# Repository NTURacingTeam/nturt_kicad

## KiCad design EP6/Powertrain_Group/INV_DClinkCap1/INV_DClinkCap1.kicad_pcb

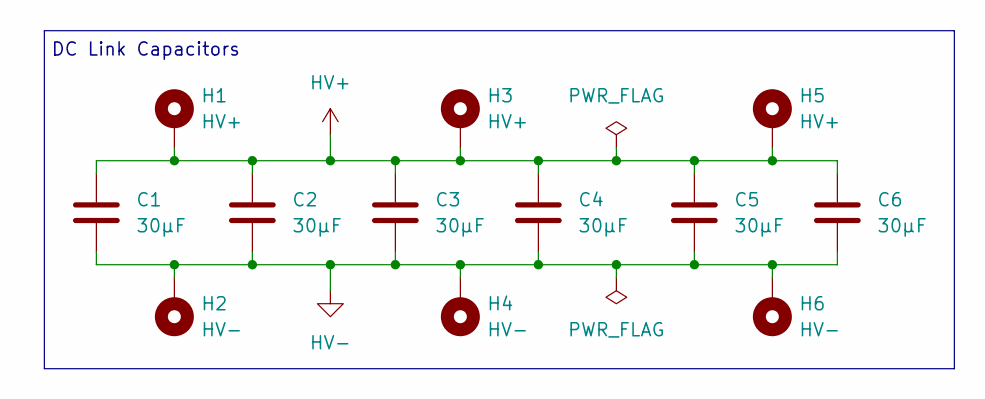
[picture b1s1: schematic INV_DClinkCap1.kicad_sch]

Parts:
C1, C2, C3, C4, C5, C6: 30µF; C4AQJBW5300M3JJ
H1, H3, H5: HV+; MountingHole_5.5mm_Pad_Via_15mm_square
H2, H4, H6: HV-; MountingHole_5.5mm_Pad_Via_15mm_square

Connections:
HV+: C1.1, C2.1, C3.1, C4.1, C5.1, C6.1, H1.1, H3.1, H5.1
HV-: C1.2, C2.2, C3.2, C4.2, C5.2, C6.2, H2.1, H4.1, H6.1

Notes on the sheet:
DC Link Capacitors

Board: 4 copper layers, 12 parts (3 on the bottom side), 2 nets, no tracks yet.

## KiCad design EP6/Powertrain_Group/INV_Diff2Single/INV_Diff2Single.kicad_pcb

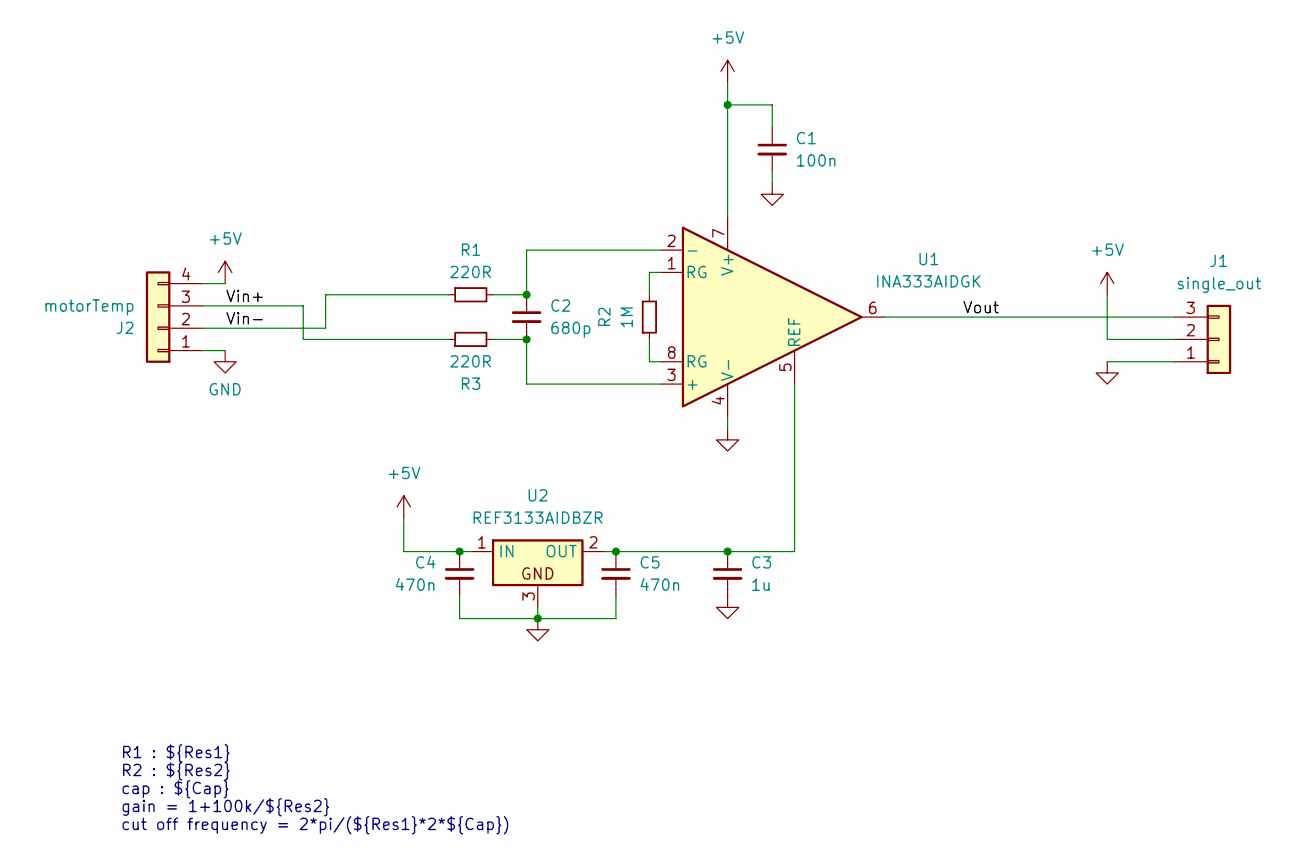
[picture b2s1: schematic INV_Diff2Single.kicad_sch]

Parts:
C1: 100n; C_0402_1005Metric
C2: 680p; C_0402_1005Metric
C3: 1u; C_0402_1005Metric
C4, C5: 470n; C_0603_1608Metric
J1: single_out; PinHeader_1x03_P2.00mm_Horizontal
J2: motorTemp; PinHeader_1x04_P2.54mm_Horizontal
R1, R3: 220R; R_0402_1005Metric
R2: 1M; R_0402_1005Metric
U1: INA333AIDGK; MSOP-8_3x3mm_P0.65mm
U2: REF3133AIDBZR; SOT-23

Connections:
+5V: C1.1, C4.1, J1.2, J2.4, U1.7 (V+), U2.1 (IN)
/Vin+: J2.3, R3.1
/Vin-: J2.2, R1.1
/Vout: J1.3, U1.6
GND: C1.2, C3.2, C4.2, C5.2, J1.1, J2.1, U1.4 (V-), U2.3
unnamed: R2.1, U1.8 (RG)
unnamed: R2.2, U1.1 (RG)
unnamed: C2.2, R3.2, U1.3 (+)
unnamed: C2.1, R1.2, U1.2 (-)
unnamed: C3.1, C5.1, U1.5 (REF), U2.2 (OUT)

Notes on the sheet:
R1 : ${Res1} R2 : ${Res2} cap : ${Cap} gain = 1+100k/${Res2} cut off frequency = 2*pi/(${Res1}*2*${Cap})

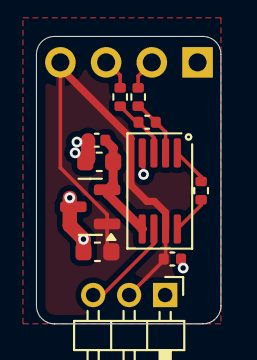
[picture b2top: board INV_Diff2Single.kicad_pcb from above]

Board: 2 copper layers, 10.2 x 16.0 mm, 12 parts (1 on the bottom side), 10 nets.

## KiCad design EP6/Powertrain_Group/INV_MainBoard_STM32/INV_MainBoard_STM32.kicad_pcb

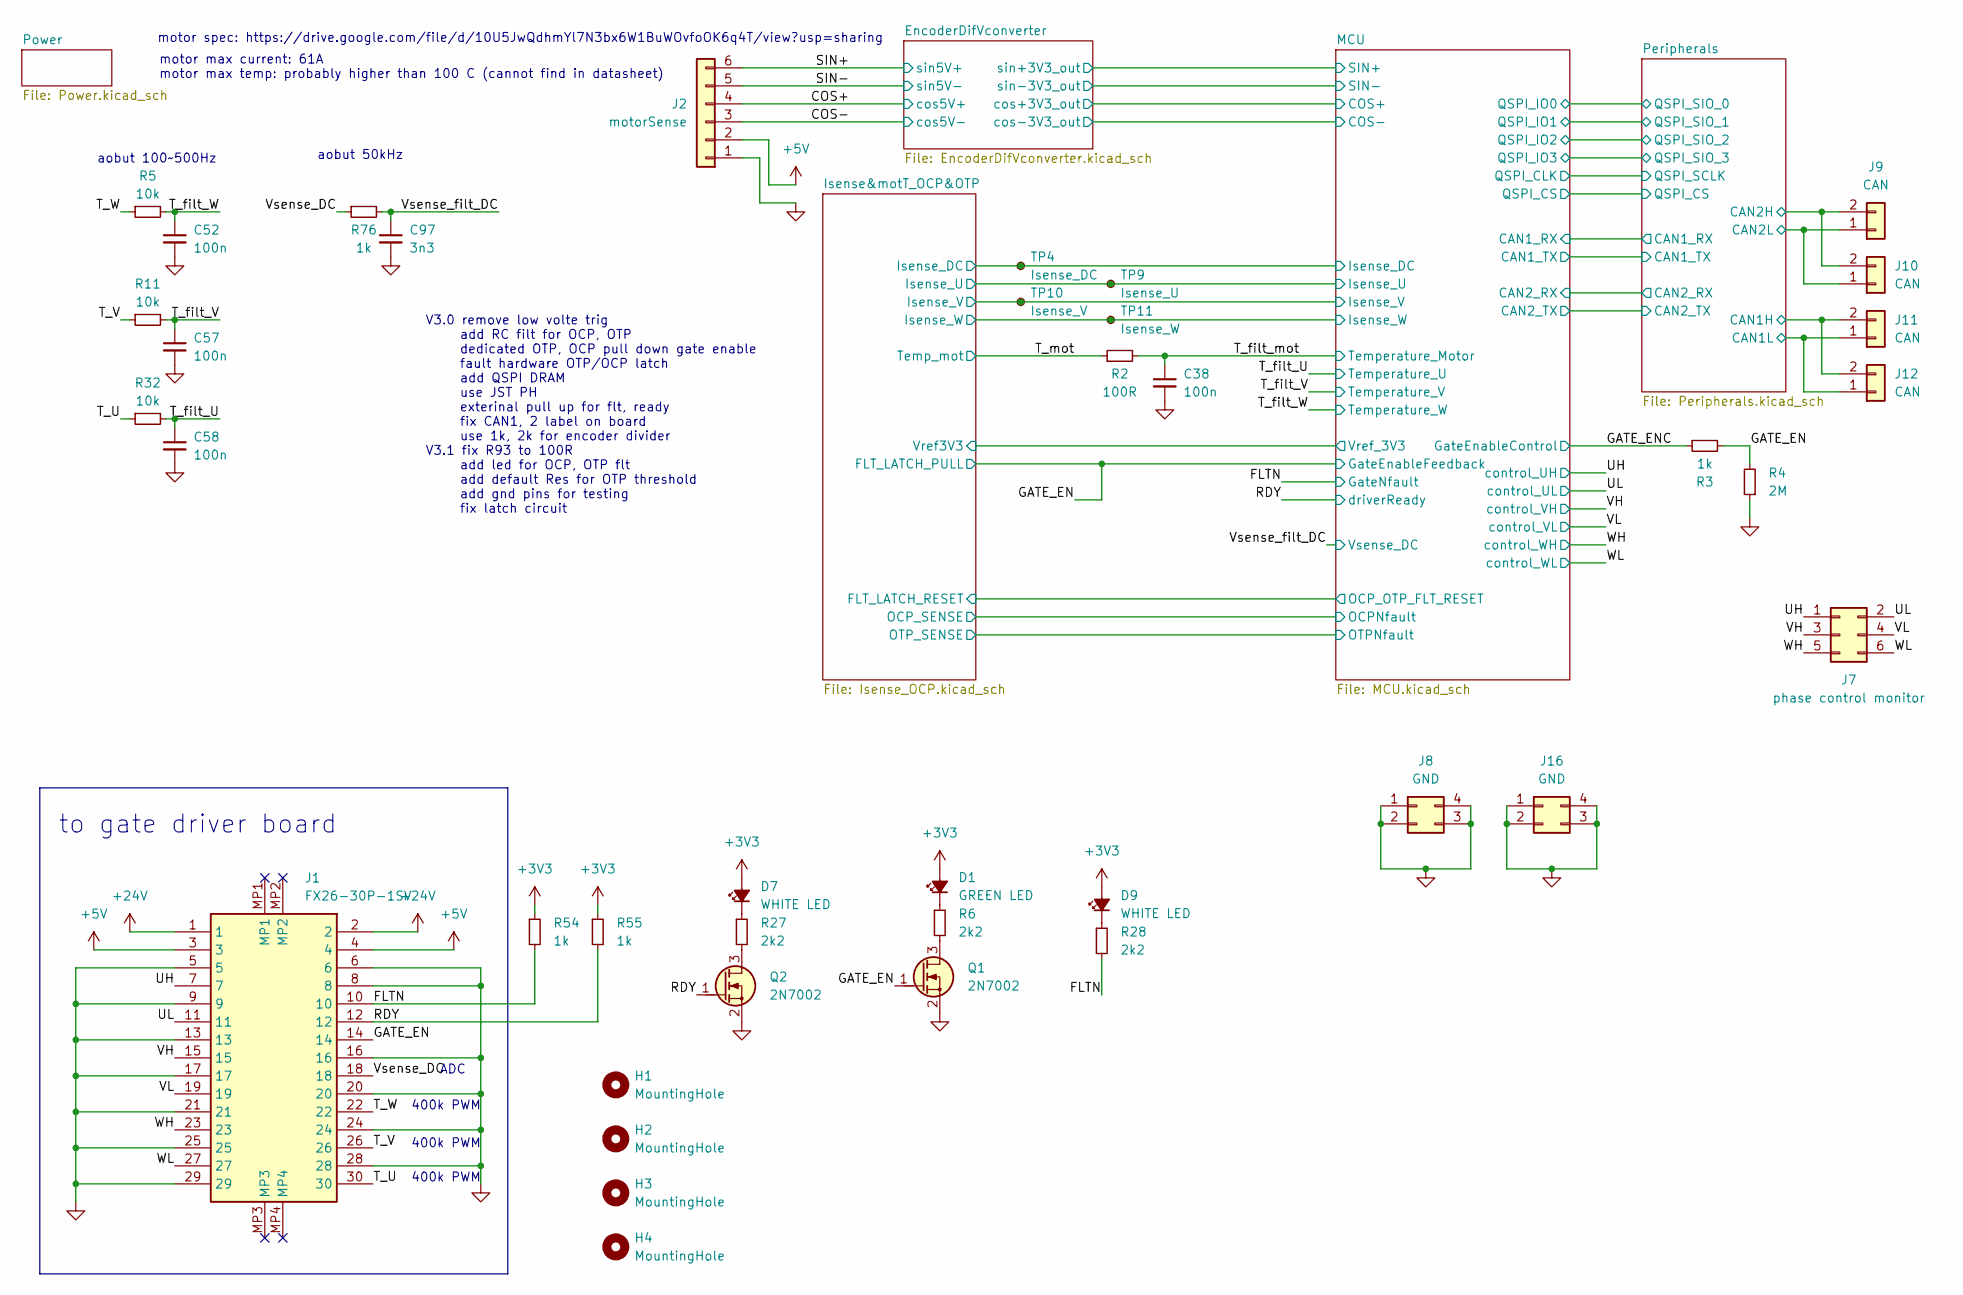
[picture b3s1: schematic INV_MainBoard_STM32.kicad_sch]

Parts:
C38, C52, C57, C58: 100n; C_0402_1005Metric
C97: 3n3; C_0402_1005Metric
D1: GREEN LED; LED_0805_2012Metric
D7, D9: WHITE LED; LED_0805_2012Metric
H1, H2, H3, H4: MountingHole; MountingHole_3.2mm_M3
J1: FX26-30P-1SV; FX2630P1SV; Mouser Part Number 798-FX2630P1SV
J2: motorSense; JST_PH_B6B-PH-K_1x06_P2.00mm_Vertical
J7: phase control monitor; PinHeader_2x03_P2.54mm_Vertical
J8, J16: GND; PinHeader_2x02_P2.54mm_Vertical
J9, J10, J11, J12: CAN; JST_XH_B2B-XH-A_1x02_P2.50mm_Vertical
Q1, Q2: 2N7002; SOT-23
R2: 100R; R_0402_1005Metric
R3, R54, R55, R76: 1k; R_0402_1005Metric
R4: 2M; R_0603_1608Metric
R5, R11, R32: 10k; R_0402_1005Metric
R6, R27, R28: 2k2; R_0402_1005Metric
TP4: Isense_DC; TestPoint_Pad_D1.0mm
TP9: Isense_U; TestPoint_Pad_D1.0mm
TP10: Isense_V; TestPoint_Pad_D1.0mm
TP11: Isense_W; TestPoint_Pad_D1.0mm

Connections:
+3V3: D1.2 (A), D7.2 (A), D9.2 (A), R54.1, R55.1; also elsewhere on the board
+5V: J1.3, J1.4, J2.2; also elsewhere on the board
+24V: J1.1, J1.2; also elsewhere on the board
/COS+: J2.4; also elsewhere on the board
/COS-: J2.3; also elsewhere on the board
/FLTN: J1.10, R28.2, R54.2; also elsewhere on the board
/GATE_EN: J1.14, Q1.1 (G), R3.2, R4.2; also elsewhere on the board
/GATE_ENC: R3.1; also elsewhere on the board
/Isense&motT_OCP&OTP/Isense_DC: TP4.1; also elsewhere on the board
/Isense&motT_OCP&OTP/Isense_U: TP9.1; also elsewhere on the board
/Isense&motT_OCP&OTP/Isense_V: TP10.1; also elsewhere on the board
/Isense&motT_OCP&OTP/Isense_W: TP11.1; also elsewhere on the board
/Peripherals/CAN1H: J11.2, J12.2; also elsewhere on the board
/Peripherals/CAN1L: J11.1, J12.1; also elsewhere on the board
/Peripherals/CAN2H: J9.2, J10.2; also elsewhere on the board
/Peripherals/CAN2L: J9.1, J10.1; also elsewhere on the board
/RDY: J1.12, Q2.1 (G), R55.2; also elsewhere on the board
/SIN+: J2.6; also elsewhere on the board
/SIN-: J2.5; also elsewhere on the board
/T_U: J1.30, R32.1
/T_V: J1.26, R11.1
/T_W: J1.22, R5.1
/T_filt_U: C58.1, R32.2; also elsewhere on the board
/T_filt_V: C57.1, R11.2; also elsewhere on the board
/T_filt_W: C52.1, R5.2; also elsewhere on the board
/T_filt_mot: C38.1, R2.2; also elsewhere on the board
/T_mot: R2.1; also elsewhere on the board
/UH: J1.7, J7.1; also elsewhere on the board
/UL: J1.11, J7.2; also elsewhere on the board
/VH: J1.15, J7.3; also elsewhere on the board
/VL: J1.19, J7.4; also elsewhere on the board
/Vsense_DC: J1.18, R76.1
/Vsense_filt_DC: C97.1, R76.2; also elsewhere on the board
/WH: J1.23, J7.5; also elsewhere on the board
/WL: J1.27, J7.6; also elsewhere on the board
GND: C38.2, C52.2, C57.2, C58.2, C97.2, J1.5, J1.6, J1.8, J1.9, J1.13, J1.16, J1.17, J1.20, J1.21, J1.24, J1.25, J1.28, J1.29, J2.1, J8.1, J8.2, J8.3, J8.4, J16.1, J16.2, J16.3, J16.4, Q1.2 (S), Q2.2 (S), R4.1; also elsewhere on the board
unnamed: D1.1 (K), R6.1
unnamed: D7.1 (K), R27.1
unnamed: D9.1 (K), R28.1
unnamed: Q1.3 (D), R6.2
unnamed: Q2.3 (D), R27.2

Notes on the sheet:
motor spec: https://drive.google.com/file/d/10U5JwQdhmYl7N3bx6W1BuWOvfoOK6q4T/view?usp=sharing
400k PWM
to gate driver board
motor max current: 61A motor max temp: probably higher than 100 C (cannot find in datasheet)
V3.0 remove low volte trig add RC filt for OCP, OTP dedicated OTP, OCP pull down gate enable fault hardware OTP/OCP latch add QSPI DRAM use JST PH exterinal pull up for flt, ready fix CAN1, 2 label on board use 1k, 2k for encoder divider V3.1 fix R93 to 100R add led for OCP, OTP flt add default Res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
aobut 50kHz
aobut 100~500Hz
ADC

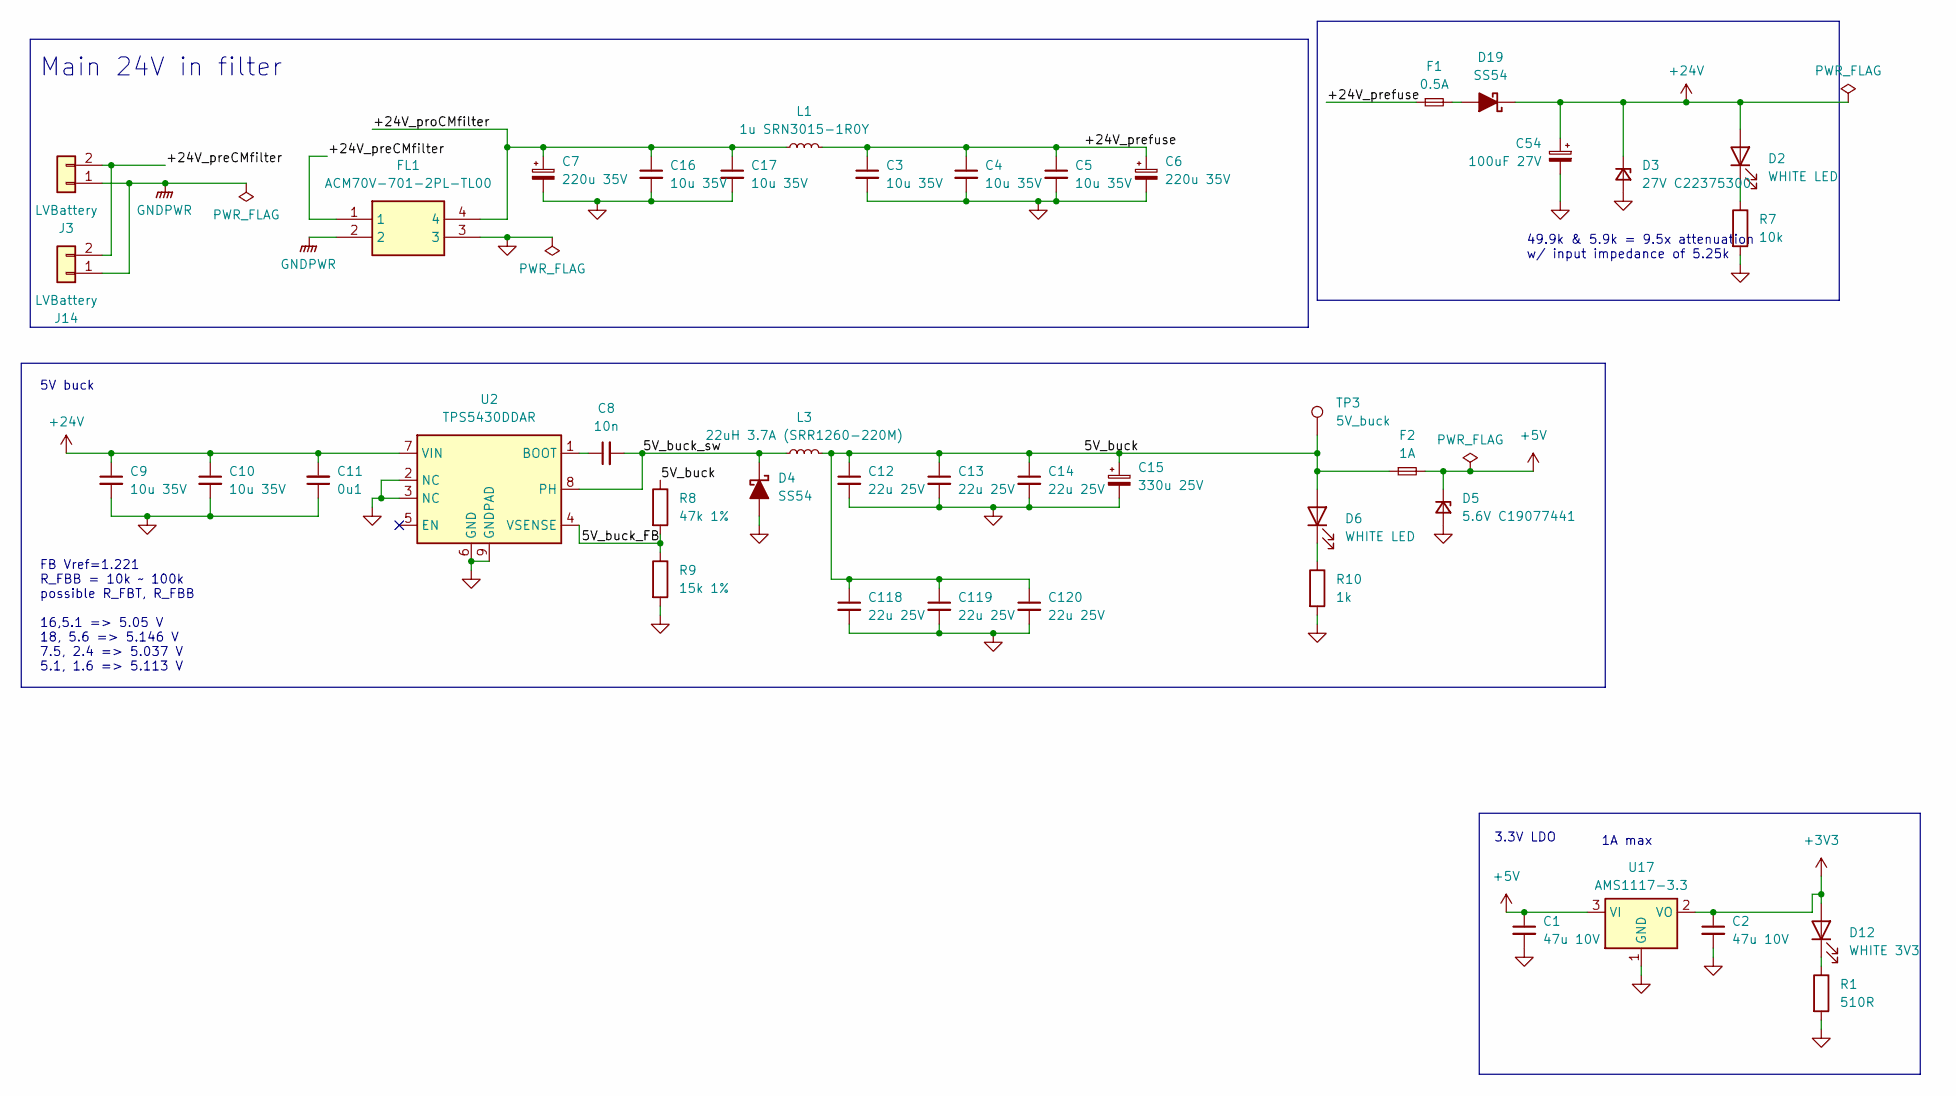
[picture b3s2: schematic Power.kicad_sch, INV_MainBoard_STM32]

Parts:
C1, C2: 47u 10V; C_1206_3216Metric
C3, C4, C5, C9, C10, C16, C17: 10u 35V; C_1206_3216Metric
C6, C7: 220u 35V; CP_Radial_D8.0mm_P3.80mm
C8: 10n; C_0603_1608Metric
C11: 0u1; C_0603_1608Metric
C12, C13, C14, C118, C119, C120: 22u 25V; C_1206_3216Metric
C15: 330u 25V; CP_Radial_D8.0mm_P3.80mm
C54: 100uF 27V; CP_Radial_D10.0mm_P5.00mm
D2, D6: WHITE LED; LED_0603_1608Metric
D3: 27V C22375300; D_SOD-323
D4, D19: SS54; D_SMA
D5: 5.6V C19077441; D_SOD-323
D12: WHITE 3V3; LED_0603_1608Metric
F1: 0.5A; Fuse_1206_3216Metric
F2: 1A; Fuse_1206_3216Metric
FL1: ACM70V-701-2PL-TL00; ACM70V7012PLTL00; Mouser Part Number 810-ACM70V7012PLTL00
J3, J14: LVBattery; JST_VH_B2P-VH_1x02_P3.96mm_Vertical
L1: 1u SRN3015-1R0Y; L_Wuerth_MAPI-3015
L3: 22uH 3.7A (SRR1260-220M); SRR1260A220M
R1: 510R; R_0402_1005Metric
R7: 10k; R_0402_1005Metric
R8: 47k 1%; R_0603_1608Metric
R9: 15k 1%; R_0603_1608Metric
R10: 1k; R_0402_1005Metric
TP3: 5V_buck; TestPoint_Pad_D1.0mm
U2: TPS5430DDAR; TI_SO-PowerPAD-8_ThermalVias
U17: AMS1117-3.3; SOT-223-3_TabPin2

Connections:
+3V3: C2.1, D12.2 (A), U17.2 (VO); also elsewhere on the board
+5V: C1.1, D5.1 (K), F2.2, U17.3 (VI); also elsewhere on the board
+24V: C9.1, C10.1, C11.2, C54.1, D2.2 (A), D3.1 (K), D19.1 (K), U2.7 (VIN); also elsewhere on the board
/Power/5V_buck: C12.1, C13.1, C14.1, C15.1, C118.1, C119.1, C120.1, D6.2 (A), F2.1, L3.2, R8.1, TP3.1
/Power/5V_buck_FB: R8.2, R9.1, U2.4 (VSENSE)
/Power/5V_buck_sw: C8.2, D4.1 (K), L3.1, U2.8 (PH)
/Power/+24V_preCMfilter: FL1.1, J3.2, J14.2
/Power/+24V_prefuse: C3.1, C4.1, C5.1, C6.1, F1.1, L1.2
/Power/+24V_proCMfilter: C7.1, C16.1, C17.1, FL1.4, L1.1
GND: C1.2, C2.2, C3.2, C4.2, C5.2, C6.2, C7.2, C9.2, C10.2, C11.1, C12.2, C13.2, C14.2, C15.2, C16.2, C17.2, C54.2, C118.2, C119.2, C120.2, D3.2 (A), D4.2 (A), D5.2 (A), FL1.3, R1.2, R7.2, R9.2, R10.2, U2.2 (NC), U2.3 (NC), U2.6 (GND), U2.9 (GNDPAD), U17.1 (GND); also elsewhere on the board
GNDPWR: FL1.2, J3.1, J14.1
unnamed: D2.1 (K), R7.1
unnamed: D6.1 (K), R10.1
unnamed: D12.1 (K), R1.1
unnamed: D19.2 (A), F1.2
unnamed: C8.1, U2.1 (BOOT)

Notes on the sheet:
5V buck
49.9k & 5.9k = 9.5x attenuation w/ input impedance of 5.25k
1A max
FB Vref=1.221 R_FBB = 10k ~ 100k possible R_FBT, R_FBB 16,5.1 => 5.05 V 18, 5.6 => 5.146 V 7.5, 2.4 => 5.037 V 5.1, 1.6 => 5.113 V
Main 24V in filter
3.3V LDO

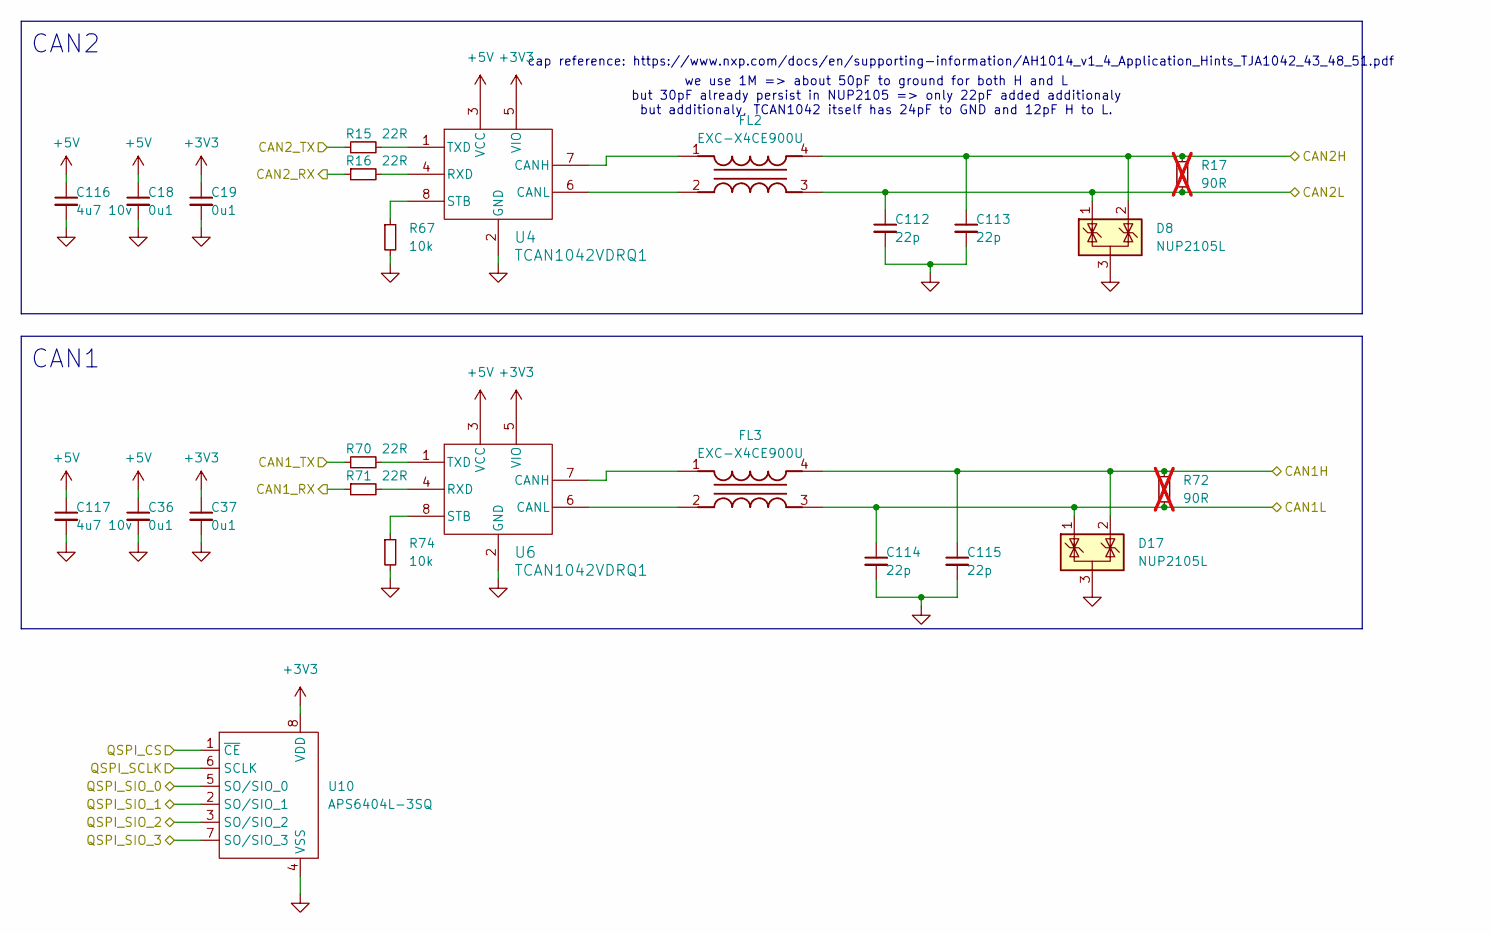
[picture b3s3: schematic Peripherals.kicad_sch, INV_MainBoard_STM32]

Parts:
C18, C19, C36, C37: 0u1; C_0402_1005Metric
C112, C113, C114, C115: 22p; C_0402_1005Metric
C116, C117: 4u7 10v; C_0402_1005Metric
D8, D17: NUP2105L; SOT-23
FL2, FL3: EXC-X4CE900U; EXCX4CE900U; Mouser Part Number 667-EXC-X4CE900U
R15, R16, R70, R71: 22R; R_0402_1005Metric
R17, R72: 90R; R_0402_1005Metric; not fitted
R67, R74: 10k; R_0402_1005Metric
U4, U6: TCAN1042VDRQ1; SOIC-8_3.9x4.9mm_P1.27mm
U10: APS6404L-3SQ; SOP-8_3.76x4.96mm_P1.27mm

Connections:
+3V3: C19.1, C37.1, U4.5 (VIO), U6.5 (VIO), U10.8 (VDD); also elsewhere on the board
+5V: C18.1, C36.1, C116.1, C117.1, U4.3 (VCC), U6.3 (VCC); also elsewhere on the board
/MCU/CAN1_RX: R71.1; also elsewhere on the board
/MCU/CAN1_TX: R70.1; also elsewhere on the board
/MCU/CAN2_RX: R16.1; also elsewhere on the board
/MCU/CAN2_TX: R15.1; also elsewhere on the board
/MCU/QSPI_CLK: U10.6 (SCLK); also elsewhere on the board
/MCU/QSPI_CS: U10.1 (~CE); also elsewhere on the board
/MCU/QSPI_IO0: U10.5 (SO/SIO_0); also elsewhere on the board
/MCU/QSPI_IO1: U10.2 (SO/SIO_1); also elsewhere on the board
/MCU/QSPI_IO2: U10.3 (SO/SIO_2); also elsewhere on the board
/MCU/QSPI_IO3: U10.7 (SO/SIO_3); also elsewhere on the board
/Peripherals/CAN1H: C115.1, D17.2 (K), FL3.4, R72.1; also elsewhere on the board
/Peripherals/CAN1L: C114.1, D17.1 (K), FL3.3, R72.2; also elsewhere on the board
/Peripherals/CAN2H: C113.1, D8.2 (K), FL2.4, R17.1; also elsewhere on the board
/Peripherals/CAN2L: C112.1, D8.1 (K), FL2.3, R17.2; also elsewhere on the board
GND: C18.2, C19.2, C36.2, C37.2, C112.2, C113.2, C114.2, C115.2, C116.2, C117.2, D8.3 (A), D17.3 (A), R67.2, R74.2, U4.2 (GND), U6.2 (GND), U10.4 (VSS); also elsewhere on the board
unnamed: FL2.1, U4.7 (CANH)
unnamed: FL2.2, U4.6 (CANL)
unnamed: R16.2, U4.4 (RXD)
unnamed: R67.1, U4.8 (STB)
unnamed: R15.2, U4.1 (TXD)
unnamed: FL3.1, U6.7 (CANH)
unnamed: FL3.2, U6.6 (CANL)
unnamed: R71.2, U6.4 (RXD)
unnamed: R74.1, U6.8 (STB)
unnamed: R70.2, U6.1 (TXD)

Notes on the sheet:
CAN2
CAN1
cap reference: https://www.nxp.com/docs/en/supporting-information/AH1014_v1_4_Application_Hints_TJA1042_43_48_51.pdf
we use 1M => about 50pF to ground for both H and L but 30pF already persist in NUP2105 => only 22pF added additionaly but additionaly, TCAN1042 itself has 24pF to GND and 12pF H to L.

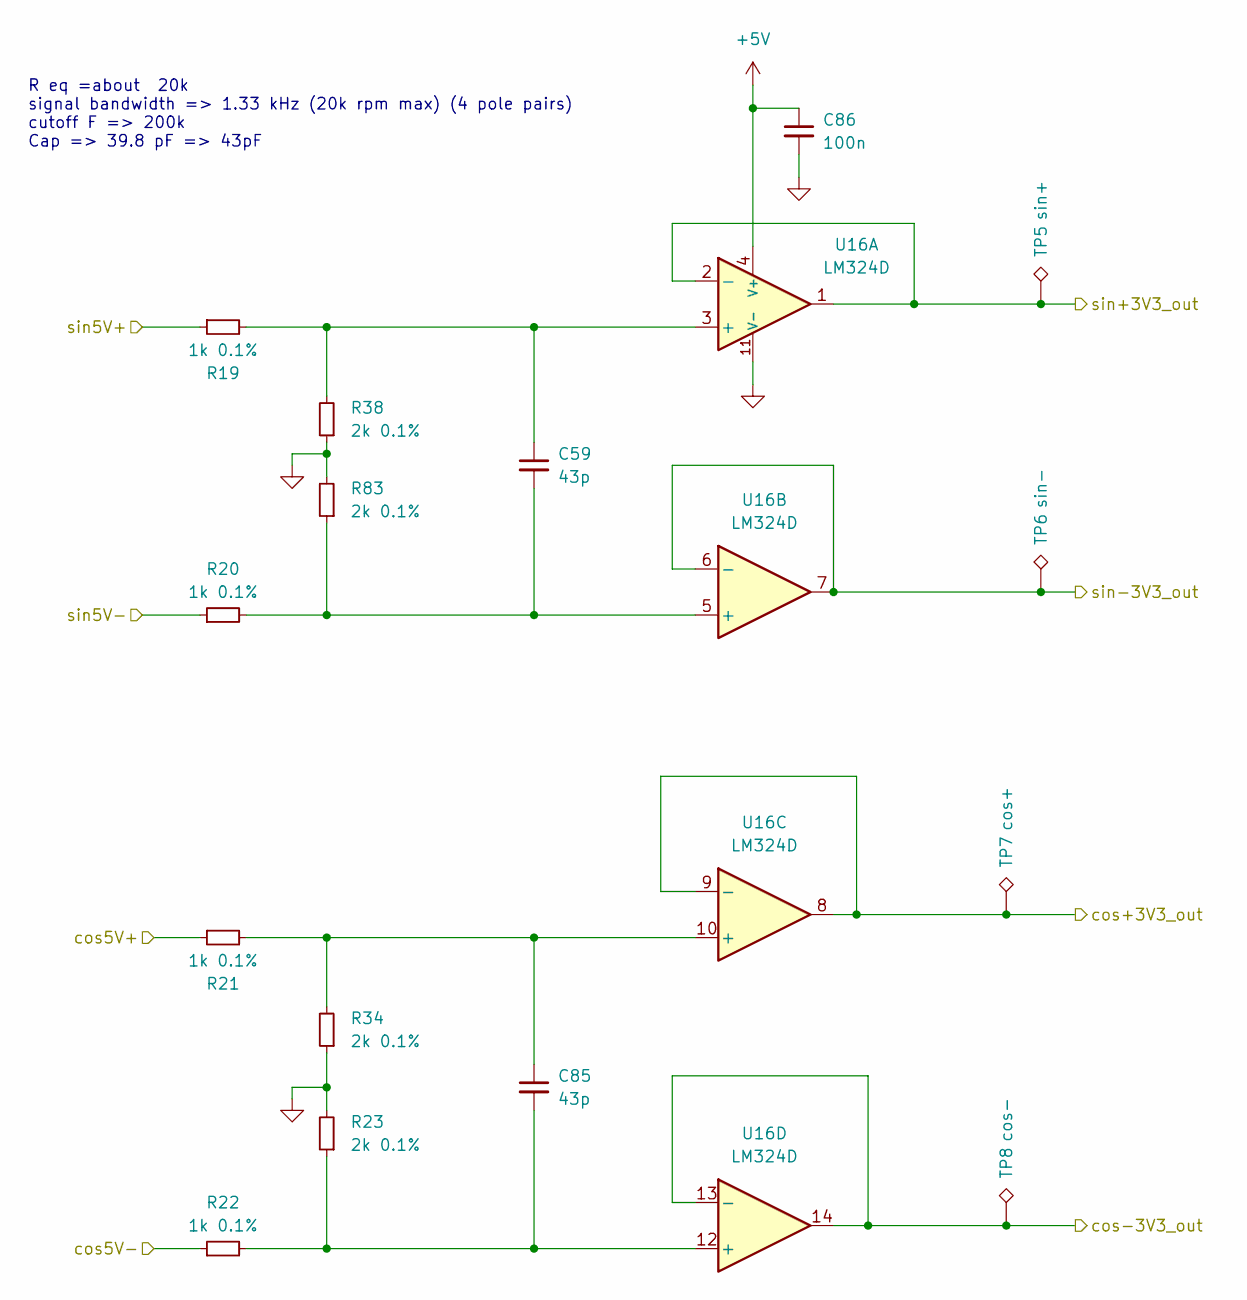
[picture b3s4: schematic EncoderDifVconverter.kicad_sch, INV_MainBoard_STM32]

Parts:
C59, C85: 43p; C_0402_1005Metric
C86: 100n; C_0402_1005Metric
R19, R20, R21, R22: 1k 0.1%; R_0402_1005Metric
R23, R34, R38, R83: 2k 0.1%; R_0402_1005Metric
TP5: sin+; TestPoint_Pad_D1.0mm
TP6: sin-; TestPoint_Pad_D1.0mm
TP7: cos+; TestPoint_Pad_D1.0mm
TP8: cos-; TestPoint_Pad_D1.0mm
U16: LM324D; SOIC-14_3.9x8.7mm_P1.27mm

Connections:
+5V: C86.1, U16.4 (V+); also elsewhere on the board
/COS+: R21.1; also elsewhere on the board
/COS-: R22.1; also elsewhere on the board
/EncoderDifVconverter/cos+3V3_out: TP7.1, U16.8, U16.9 (-); also elsewhere on the board
/EncoderDifVconverter/cos-3V3_out: TP8.1, U16.13 (-), U16.14; also elsewhere on the board
/EncoderDifVconverter/sin+3V3_out: TP5.1, U16.1, U16.2 (-); also elsewhere on the board
/EncoderDifVconverter/sin-3V3_out: TP6.1, U16.6 (-), U16.7; also elsewhere on the board
/SIN+: R19.1; also elsewhere on the board
/SIN-: R20.1; also elsewhere on the board
GND: C86.2, R23.2, R34.1, R38.1, R83.2, U16.11 (V-); also elsewhere on the board
unnamed: C59.1, R19.2, R38.2, U16.3 (+)
unnamed: C59.2, R20.2, R83.1, U16.5 (+)
unnamed: C85.1, R21.2, R34.2, U16.10 (+)
unnamed: C85.2, R22.2, R23.1, U16.12 (+)

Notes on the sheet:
R eq =about 20k signal bandwidth => 1.33 kHz (20k rpm max) (4 pole pairs) cutoff F => 200k Cap => 39.8 pF => 43pF

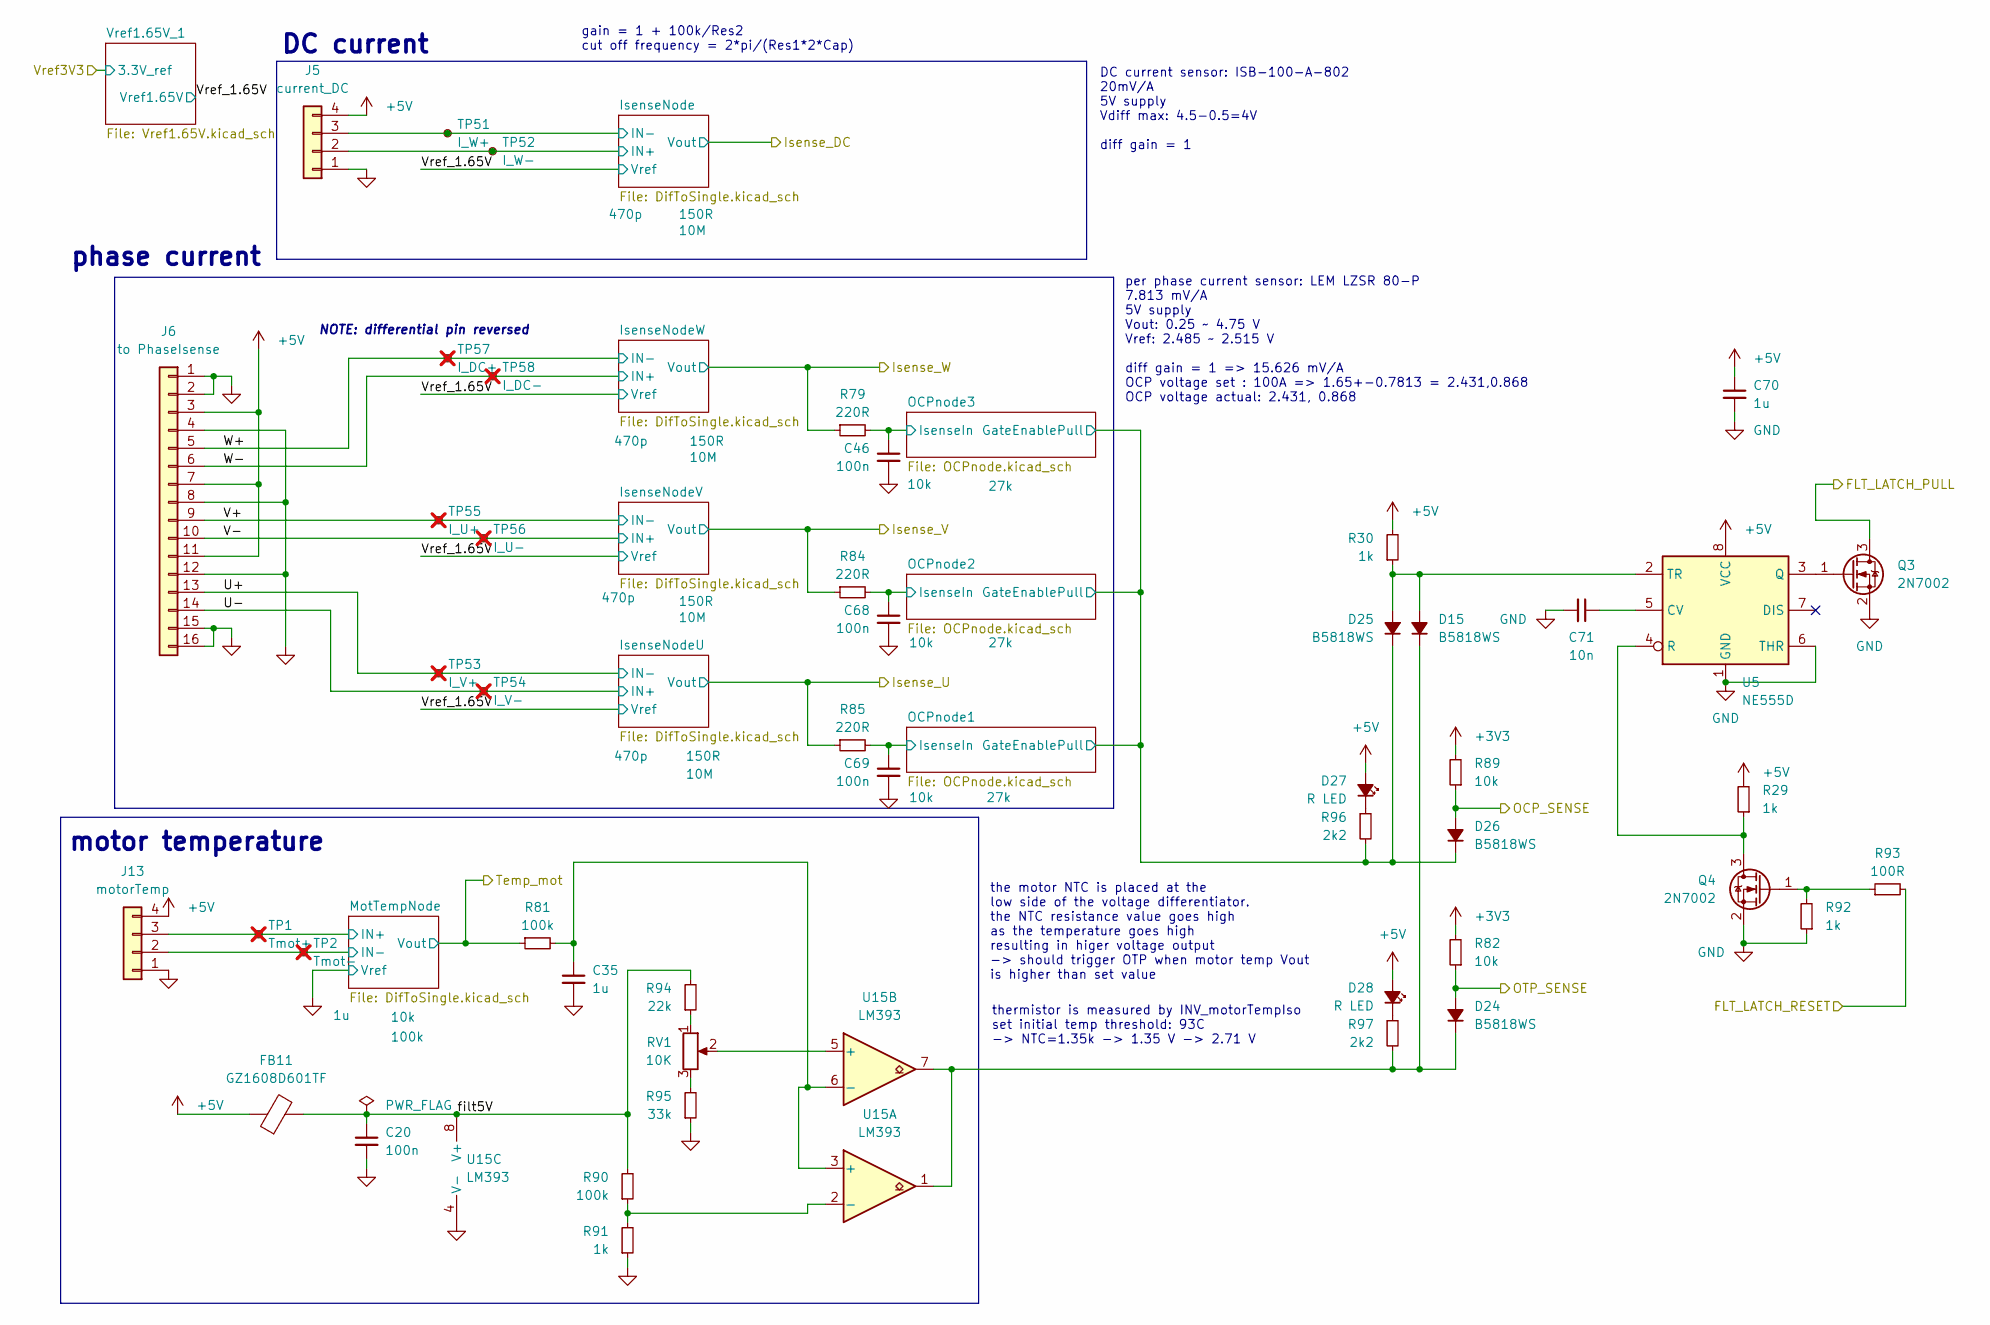
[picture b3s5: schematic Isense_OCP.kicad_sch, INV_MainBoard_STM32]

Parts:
C20, C46, C68, C69: 100n; C_0402_1005Metric
C35, C70: 1u; C_0402_1005Metric
C71: 10n; C_0402_1005Metric
D15, D24, D25, D26: B5818WS; D_SOD-323
D27, D28: R LED; LED_0603_1608Metric
FB11: GZ1608D601TF; C_0603_1608Metric
J5: current_DC; JST_PH_B4B-PH-K_1x04_P2.00mm_Vertical; Part Number 1-0401FBV0T
J6: to PhaseIsense; PinHeader_1x16_P2.54mm_Horizontal
J13: motorTemp; JST_PH_B4B-PH-K_1x04_P2.00mm_Vertical
Q3, Q4: 2N7002; SOT-23
R29, R30, R91, R92: 1k; R_0402_1005Metric
R79, R84, R85: 220R; R_0402_1005Metric
R81, R90: 100k; R_0402_1005Metric
R82, R89: 10k; R_0402_1005Metric
R93: 100R; R_0402_1005Metric
R94: 22k; R_0402_1005Metric
R95: 33k; R_0402_1005Metric
R96, R97: 2k2; R_0402_1005Metric
RV1: 10K; Throughhole Potentiometer 3296W
TP1: Tmot+; TestPoint_Pad_D1.0mm; not fitted
TP2: Tmot-; TestPoint_Pad_D1.0mm; not fitted
TP51: I_W+; TestPoint_Pad_D1.0mm
TP52: I_W-; TestPoint_Pad_D1.0mm
TP53: I_V+; TestPoint_Pad_D1.0mm; not fitted
TP54: I_V-; TestPoint_Pad_D1.0mm; not fitted
TP55: I_U+; TestPoint_Pad_D1.0mm; not fitted
TP56: I_U-; TestPoint_Pad_D1.0mm; not fitted
TP57: I_DC+; TestPoint_Pad_D1.0mm; not fitted
TP58: I_DC-; TestPoint_Pad_D1.0mm; not fitted
U5: NE555D; SOIC-8_3.9x4.9mm_P1.27mm
U15: LM393; SOIC-8_3.9x4.9mm_P1.27mm

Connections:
+3V3: R82.2, R89.2; also elsewhere on the board
+5V: C70.1, D27.2 (A), D28.2 (A), FB11.1, J5.4, J6.3, J6.7, J6.11, J13.4, R29.2, R30.2, U5.8 (VCC); also elsewhere on the board
/GATE_EN: Q3.3 (D); also elsewhere on the board
/Isense&motT_OCP&OTP/FLT_LATCH_RESET: R93.2; also elsewhere on the board
/Isense&motT_OCP&OTP/IsenseNode/IN+: J5.2, TP52.1; also elsewhere on the board
/Isense&motT_OCP&OTP/IsenseNode/IN-: J5.3, TP51.1; also elsewhere on the board
/Isense&motT_OCP&OTP/Isense_U: R85.1; also elsewhere on the board
/Isense&motT_OCP&OTP/Isense_V: R84.1; also elsewhere on the board
/Isense&motT_OCP&OTP/Isense_W: R79.1; also elsewhere on the board
/Isense&motT_OCP&OTP/MotTempNode/IN+: J13.3, TP1.1; also elsewhere on the board
/Isense&motT_OCP&OTP/MotTempNode/IN-: J13.2, TP2.1; also elsewhere on the board
/Isense&motT_OCP&OTP/OCP_SENSE: D26.2 (A), R89.1; also elsewhere on the board
/Isense&motT_OCP&OTP/OCPnode1/GateEnablePull: D25.1 (K), D26.1 (K), R96.2; also elsewhere on the board
/Isense&motT_OCP&OTP/OCPnode1/IsenseIn: C69.1, R85.2; also elsewhere on the board
/Isense&motT_OCP&OTP/OCPnode2/IsenseIn: C68.1, R84.2; also elsewhere on the board
/Isense&motT_OCP&OTP/OCPnode3/IsenseIn: C46.1, R79.2; also elsewhere on the board
/Isense&motT_OCP&OTP/OTP_SENSE: D24.2 (A), R82.1; also elsewhere on the board
/Isense&motT_OCP&OTP/U+: J6.13, TP53.1; also elsewhere on the board
/Isense&motT_OCP&OTP/U-: J6.14, TP54.1; also elsewhere on the board
/Isense&motT_OCP&OTP/V+: J6.9, TP55.1; also elsewhere on the board
/Isense&motT_OCP&OTP/V-: J6.10, TP56.1; also elsewhere on the board
/Isense&motT_OCP&OTP/W+: J6.5, TP57.1; also elsewhere on the board
/Isense&motT_OCP&OTP/W-: J6.6, TP58.1; also elsewhere on the board
/Isense&motT_OCP&OTP/filt5V: C20.1, FB11.2, R90.2, R94.2, U15.8 (V+)
/T_mot: R81.1; also elsewhere on the board
GND: C20.2, C35.2, C46.2, C68.2, C69.2, C70.2, C71.2, J5.1, J6.1, J6.2, J6.4, J6.8, J6.12, J6.15, J6.16, J13.1, Q3.2 (S), Q4.2 (S), R91.1, R92.1, R95.1, U5.1 (GND), U5.6 (THR), U15.4 (V-); also elsewhere on the board
unnamed: D15.2 (A), D25.2 (A), R30.1, U5.2 (TR)
unnamed: D15.1 (K), D24.1 (K), R97.2, U15.1, U15.7
unnamed: D27.1 (K), R96.1
unnamed: D28.1 (K), R97.1
unnamed: Q3.1 (G), U5.3 (Q)
unnamed: Q4.3 (D), R29.1, U5.4 (R)
unnamed: Q4.1 (G), R92.2, R93.1
unnamed: R94.1, RV1.1
unnamed: R95.2, RV1.3
unnamed: C71.1, U5.5 (CV)
unnamed: C35.1, R81.2, U15.3 (+), U15.6 (-)
unnamed: R90.1, R91.2, U15.2 (-)
unnamed: RV1.2, U15.5 (+)

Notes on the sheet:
motor temperature
thermistor is measured by INV_motorTempIso set initial temp threshold: 93C -> NTC=1.35k -> 1.35 V -> 2.71 V
DC current sensor: ISB-100-A-802 20mV/A 5V supply Vdiff max: 4.5-0.5=4V diff gain = 1
per phase current sensor: LEM LZSR 80-P 7.813 mV/A 5V supply Vout: 0.25 ~ 4.75 V Vref: 2.485 ~ 2.515 V diff gain = 1 => 15.626 mV/A OCP voltage set : 100A => 1.65+-0.7813 = 2.431,0.868 OCP voltage actual: 2.431, 0.868
DC current
gain = 1 + 100k/Res2 cut off frequency = 2*pi/(Res1*2*Cap)
the motor NTC is placed at the low side of the voltage differentiator. the NTC resistance value goes high as the temperature goes high resulting in higer voltage output -> should trigger OTP when motor temp Vout is higher than set value
NOTE: differential pin reversed
phase current
